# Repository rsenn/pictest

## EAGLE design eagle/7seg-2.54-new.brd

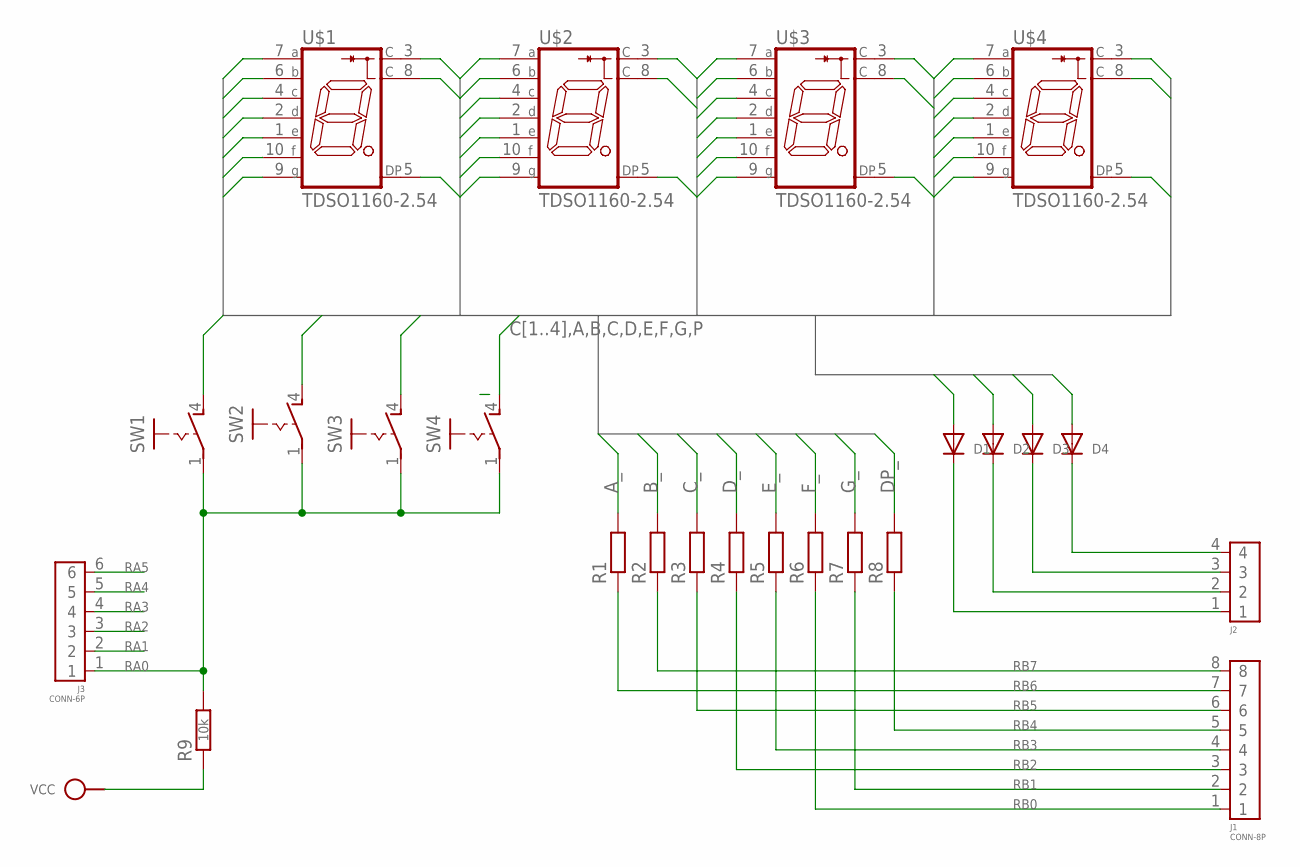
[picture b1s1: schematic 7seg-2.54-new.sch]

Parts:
D1, D2, D3, D4: 1N414834-2,5; DO34-2,5
J1: CONN-8P
J2: CONN-4P-4P; CONN-4P
J3: CONN-6P
R1, R2, R3, R4, R5, R6, R7, R8: R0202/5-V; 0202/5-V
R9: 10k; 0202/5-V
SW1, SW2, SW3, SW4: PB-1P-1T2P1T-2X3; PB-2P1T-2X3
U$1, U$2, U$3, U$4: TDSO1160-2.54; TDSX1150-2.54
VCC: SPAD

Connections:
A_: R1.2, U$1.7 (A), U$2.7 (A), U$3.7 (A), U$4.7 (A)
B_: R2.2, U$1.6 (B), U$2.6 (B), U$3.6 (B), U$4.6 (B)
C1: D1.A, SW1.4 (S), U$1.3 (C), U$1.8 (C)
C2: D2.A, SW2.4 (S), U$2.3 (C), U$2.8 (C)
C3: D3.A, SW3.4 (S), U$3.3 (C), U$3.8 (C)
C4: D4.A, SW4.4 (S), U$4.3 (C), U$4.8 (C)
C_: R3.2, U$1.4 (C), U$2.4 (C), U$3.4 (C), U$4.4 (C)
DP_: R8.2, U$1.5 (DP), U$2.5 (DP), U$3.5 (DP), U$4.5 (DP)
D_: R4.2, U$1.2 (D), U$2.2 (D), U$3.2 (D), U$4.2 (D)
E_: R5.2, U$1.1 (E), U$2.1 (E), U$3.1 (E), U$4.1 (E)
F_: R6.2, U$1.10 (F), U$2.10 (F), U$3.10 (F), U$4.10 (F)
G_: R7.2, U$1.9 (G), U$2.9 (G), U$3.9 (G), U$4.9 (G)
unnamed: D4.C, J2.4
unnamed: D3.C, J2.3
unnamed: D2.C, J2.2
unnamed: D1.C, J2.1
unnamed: R9.1, VCC.1
RA0: J3.1, R9.2, SW1.1, SW2.1, SW3.1, SW4.1
RA1: J3.2
RA2: J3.3
RA3: J3.4
RA4: J3.5
RA5: J3.6
RB0: J1.1, R6.1
RB1: J1.2, R7.1
RB2: J1.3, R4.1
RB3: J1.4, R5.1
RB4: J1.5, R8.1
RB5: J1.6, R3.1
RB6: J1.7, R1.1
RB7: J1.8, R2.1

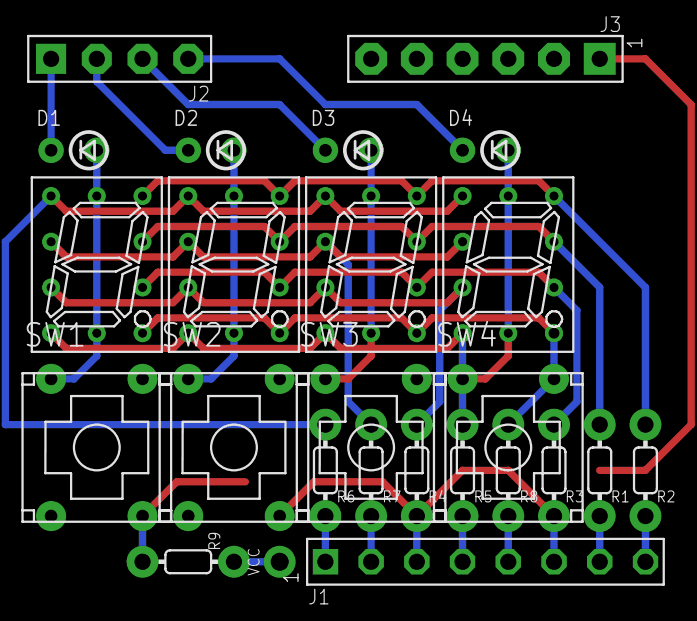
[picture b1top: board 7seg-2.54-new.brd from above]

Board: 2 copper layers, 25 parts (0 on the bottom side), 26 nets.

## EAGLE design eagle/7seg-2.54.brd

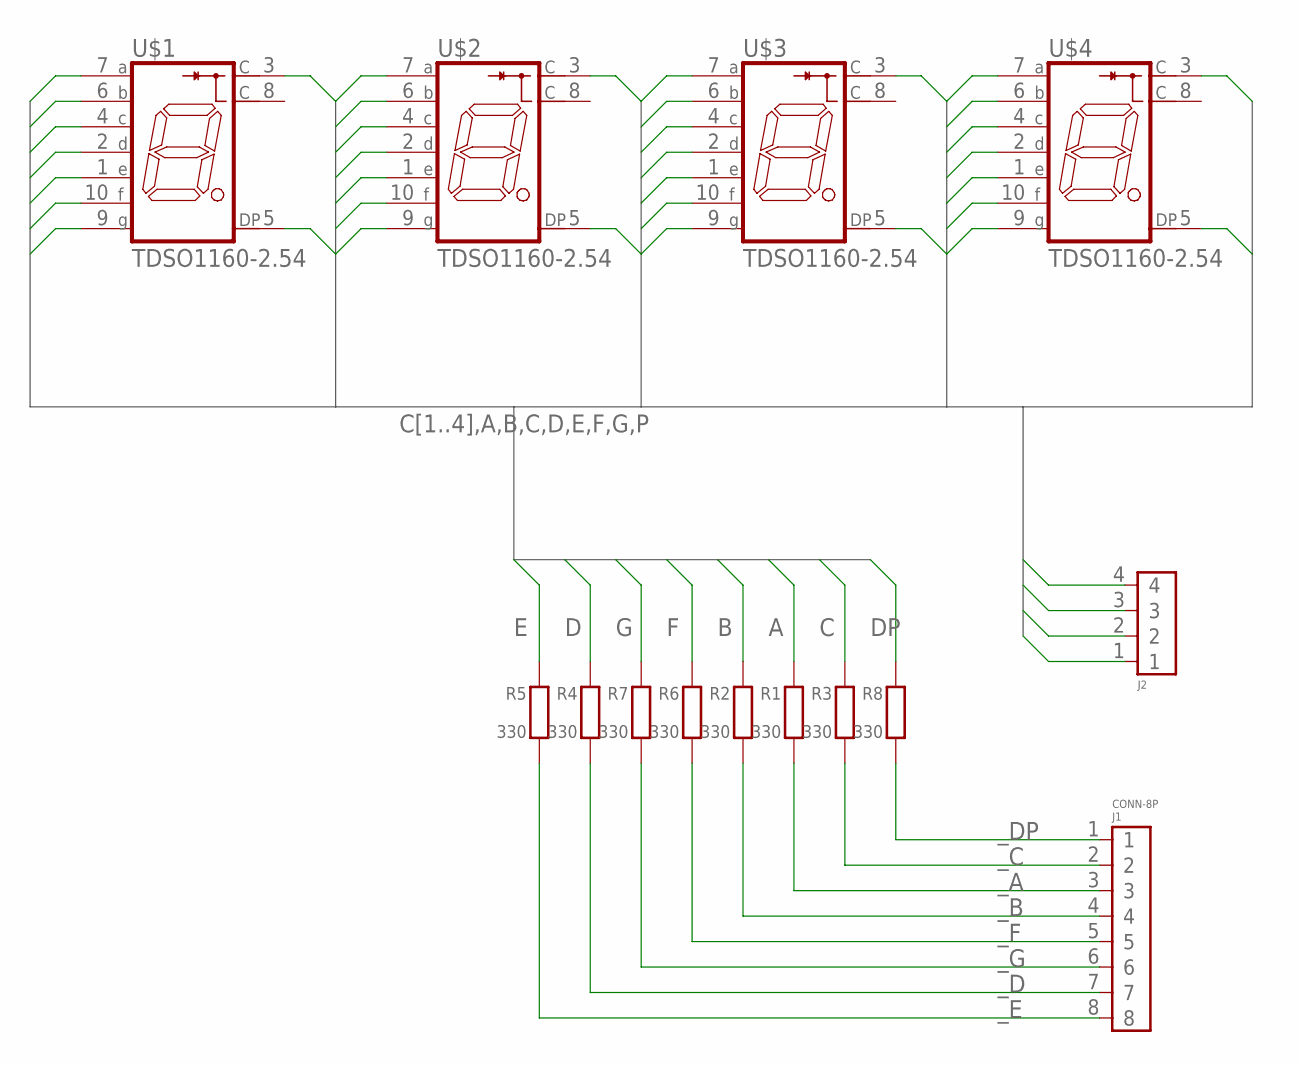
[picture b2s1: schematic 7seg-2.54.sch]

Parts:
J1: CONN-8P
J2: CONN-4P-4P; CONN-4P
R1, R2, R3, R4, R5, R6, R7, R8: 330; 0202/5-V
U$1, U$2, U$3, U$4: TDSO1160-2.54; TDSX1150-2.54

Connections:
A: R1.1 (2), U$1.7 (A), U$2.7 (A), U$3.7 (A), U$4.7 (A)
B: R2.1 (2), U$1.6 (B), U$2.6 (B), U$3.6 (B), U$4.6 (B)
C: R3.1 (2), U$1.4 (C), U$2.4 (C), U$3.4 (C), U$4.4 (C)
C1: J2.1, U$1.3 (C)
C2: J2.2, U$2.3 (C)
C3: J2.3, U$3.3 (C)
C4: J2.4, U$4.3 (C)
D: R4.1 (2), U$1.2 (D), U$2.2 (D), U$3.2 (D), U$4.2 (D)
DP: R8.1 (2), U$1.5 (DP), U$2.5 (DP), U$3.5 (DP), U$4.5 (DP)
E: R5.1 (2), U$1.1 (E), U$2.1 (E), U$3.1 (E), U$4.1 (E)
F: R6.1 (2), U$1.10 (F), U$2.10 (F), U$3.10 (F), U$4.10 (F)
G: R7.1 (2), U$1.9 (G), U$2.9 (G), U$3.9 (G), U$4.9 (G)
_A: J1.3, R1.2 (1)
_B: J1.4, R2.2 (1)
_C: J1.2, R3.2 (1)
_D: J1.7, R4.2 (1)
_DP: J1.1, R8.2 (1)
_E: J1.8, R5.2 (1)
_F: J1.5, R6.2 (1)
_G: J1.6, R7.2 (1)

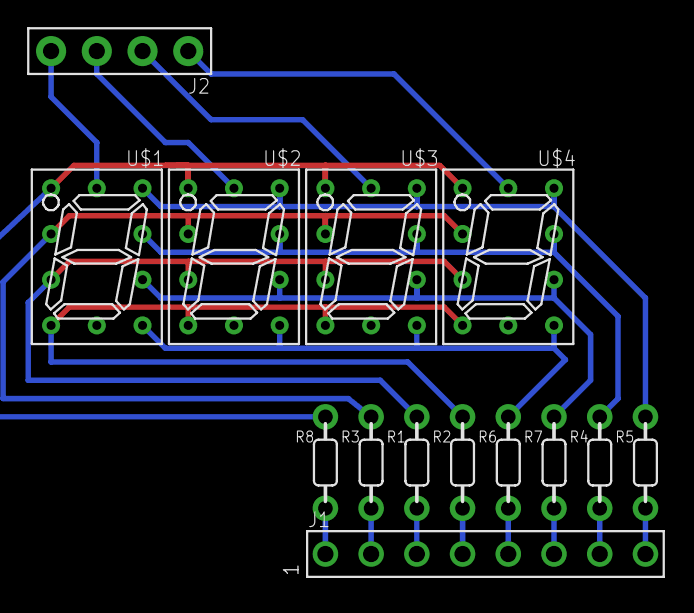
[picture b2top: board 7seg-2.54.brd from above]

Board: 2 copper layers, 14 parts (0 on the bottom side), 20 nets.

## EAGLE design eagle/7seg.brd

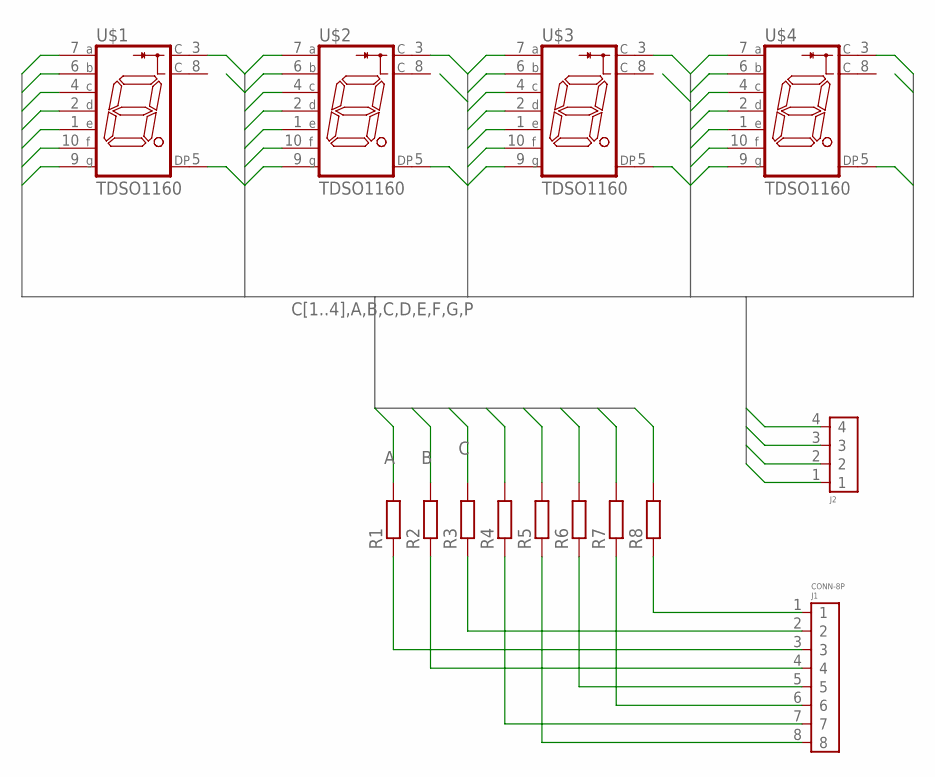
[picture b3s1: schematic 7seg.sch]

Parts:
J1: CONN-8P
J2: CONN-4P-4P; CONN-4P
R1, R2, R3, R4, R5, R6, R7, R8: R0202/7-V; 0202/7-V
U$1, U$2, U$3, U$4: TDSO1160; TDSX1150

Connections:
A: R1.2, U$1.7 (A), U$2.7 (A), U$3.7 (A), U$4.7 (A)
B: R2.2, U$1.6 (B), U$2.6 (B), U$3.6 (B), U$4.6 (B)
C: R3.2, U$1.4 (C), U$2.4 (C), U$3.4 (C), U$4.4 (C)
C1: J2.1, U$1.3 (C)
C2: J2.2, U$2.3 (C)
C3: J2.3, U$3.3 (C)
C4: J2.4, U$4.3 (C)
D: R4.2, U$1.2 (D), U$2.2 (D), U$3.2 (D), U$4.2 (D)
E: R5.2, U$1.1 (E), U$2.1 (E), U$3.1 (E), U$4.1 (E)
F: R6.2, U$1.10 (F), U$2.10 (F), U$3.10 (F), U$4.10 (F)
G: R7.2, U$1.9 (G), U$2.9 (G), U$3.9 (G), U$4.9 (G)
unnamed: J1.3, R1.1
unnamed: J1.4, R2.1
unnamed: J1.2, R3.1
unnamed: J1.7, R4.1
unnamed: J1.8, R5.1
unnamed: J1.5, R6.1
unnamed: J1.6, R7.1
unnamed: J1.1, R8.1
P: R8.2, U$1.5 (DP), U$2.5 (DP), U$3.5 (DP), U$4.5 (DP)

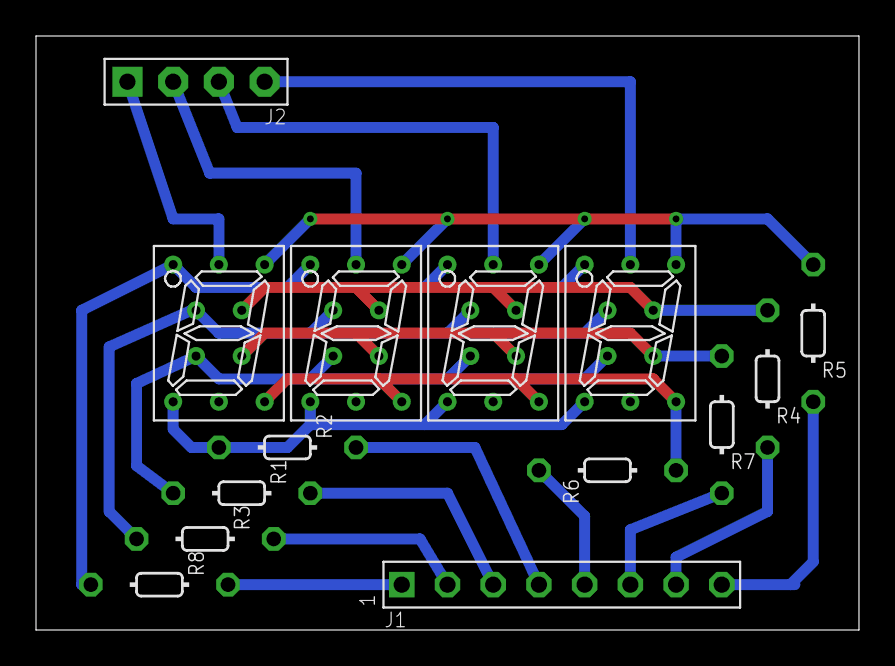
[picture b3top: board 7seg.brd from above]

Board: 2 copper layers, 45.7 x 33.0 mm, 14 parts (0 on the bottom side), 20 nets.

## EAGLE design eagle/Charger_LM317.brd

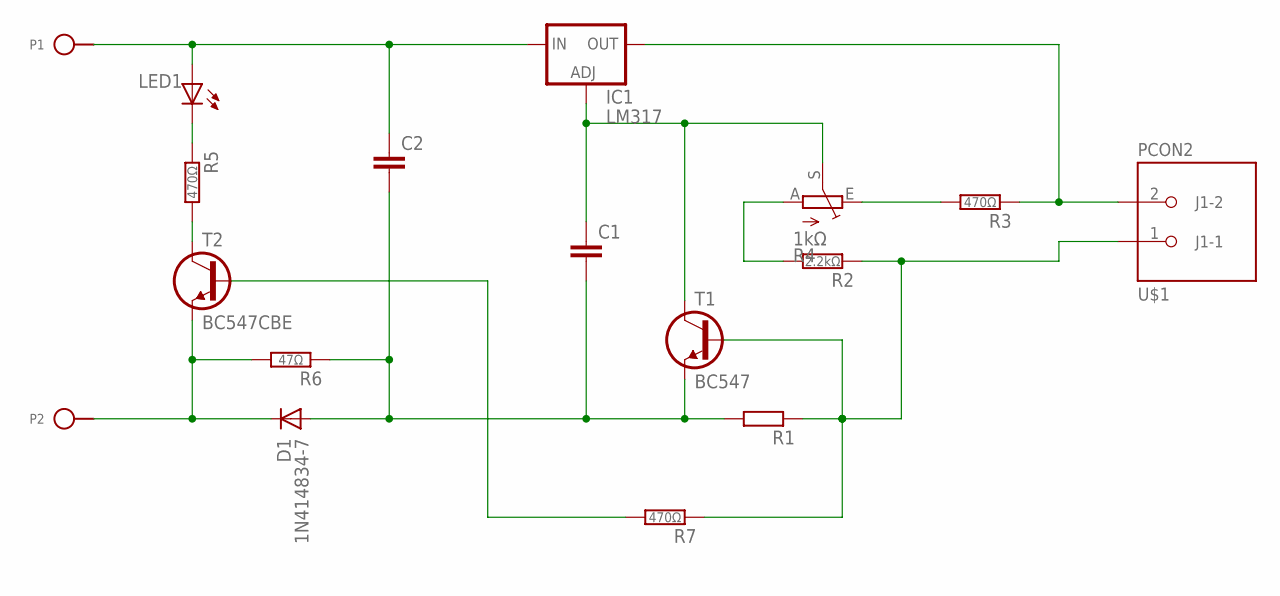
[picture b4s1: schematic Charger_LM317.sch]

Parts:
C1, C2: C050-020X036
D1: 1N414834-7; DO34-7
IC1: LM317; 317TL
LED1: LED5MM
P1: +; SPAD
P2: -; SPAD
R1: R0207/7; 0207/7
R2: 2.2kΩ; 0202/5
R3, R5, R7: 470Ω; 0202/7
R4: 1kΩ; B25P
R6: 47Ω; 0202/7
T1: BC547; TO92-CBE
T2: BC547CBE; TO92-CBE
U$1: PCON2; CON-2PIN

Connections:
ADJ: C1.1, IC1.1 (ADJ), R4.S, T1.C
GND: D1.C, P2.1, R6.2, T2.E
GND-: C1.2, C2.2, D1.A, R1.2, R6.1, T1.E
unnamed: R3.2, R4.E
unnamed: R2.2, R4.A
unnamed: R5.2, T2.C
unnamed: LED1.K (C), R5.1
unnamed: R7.2, T2.B
OUT+: IC1.2 (OUT), R3.1, U$1.2 (J1-2)
OUT-: R1.1, R2.1, R7.1, T1.B, U$1.1 (J1-1)
VCC: C2.1, IC1.3 (IN), LED1.A, P1.1

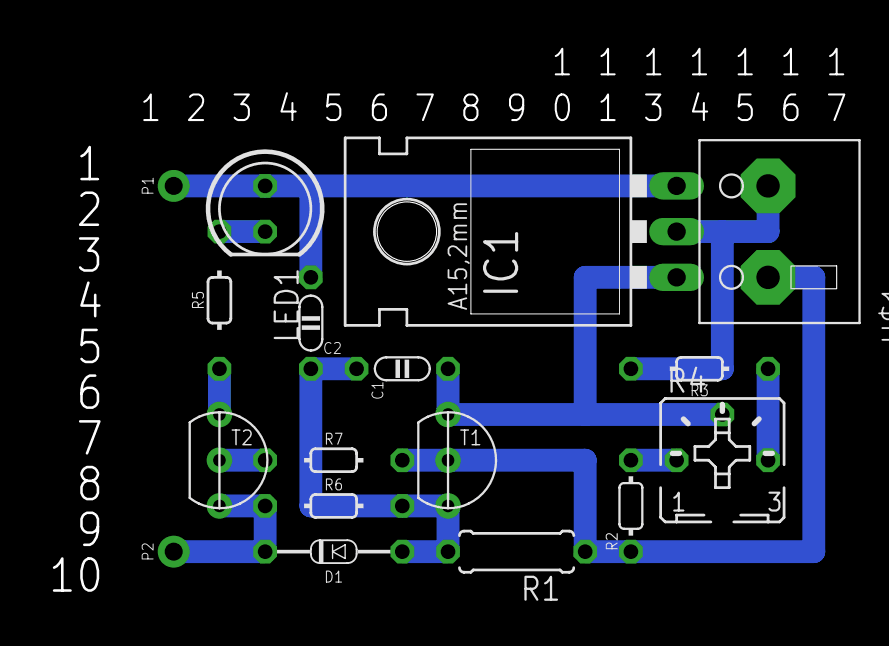
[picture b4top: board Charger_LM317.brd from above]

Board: 2 copper layers, 17 parts (0 on the bottom side), 11 nets.

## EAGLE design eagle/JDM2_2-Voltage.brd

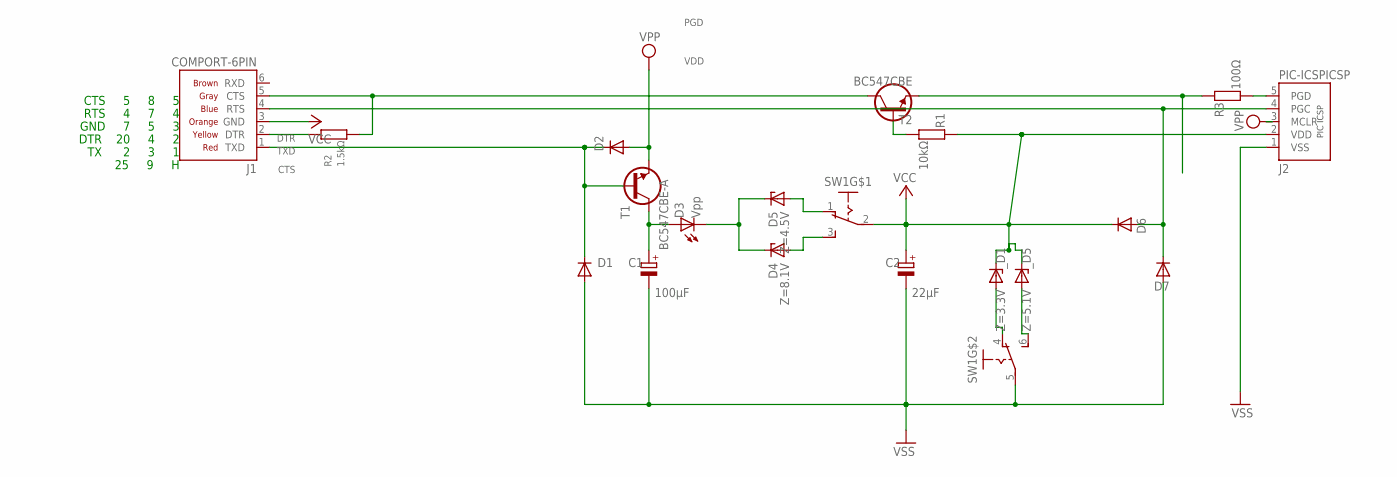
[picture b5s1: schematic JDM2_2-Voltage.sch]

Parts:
C1: 100μF; E5-4
C2: 22μF; E2,5-4
D1, D2: 1N4148; DO34-5
D3: Vpp; LED3MM
D4: Z=8.1V; DO34Z5
D5: Z=4.5V; DO34Z5
D6, D7: 1N4148; DO34-7
J1: COMPORT-6PIN; RS232-6PIN
J2: PIC-ICSPICSP; PIC-ICSP
R1: 10kΩ; 0202/7
R2: 1.5kΩ; 0202/7
R3: 100Ω; 0202/5
SW1: SL-SW-2P-2T-S; SLSW-2P2T-H
T1: BC547CBE-A; TO92-CBE-A
T2: BC547CBE; TO92-CBE
_D1: Z=3.3V; DO34Z5
_D5: Z=5.1V; DO34Z5

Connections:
/MCLR: D2.A, J2.3 (MCLR), T1.E
CLK: D6.A, D7.C, J1.4 (RTS), J2.4 (PGC)
CTS: J1.5 (CTS), R2.2, T2.C
DATA: R3.2, T2.E
DTR: J1.2 (DTR), R2.1
unnamed: R1.1, T2.B
unnamed: SW1.4 (O), _D1.A
unnamed: SW1.6 (S), _D5.A
unnamed: D5.A, SW1.1 (O)
unnamed: D3.K (C), D4.C, D5.C
unnamed: D4.A, SW1.3 (S)
PGD: J2.5 (PGD), R3.1
TXD: D1.C, D2.C, J1.1 (TXD), T1.B
VDD: C2.+, D6.C, J1.3 (GND), J2.2 (VDD), R1.2, SW1.2, _D1.C, _D5.C
VPP: C1.+, D3.A, T1.C
VSS: C1.-, C2.-, D1.A, D7.A, J2.1 (VSS), SW1.5

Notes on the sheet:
DTR 20 4 2
TX 2 3 1
CTS 5 8 5
GND 7 5 3
RTS 4 7 4
25 9 H

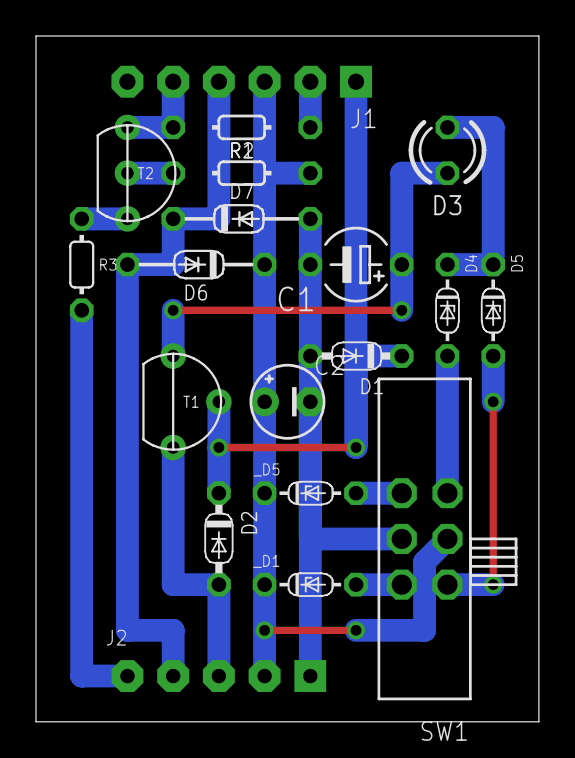
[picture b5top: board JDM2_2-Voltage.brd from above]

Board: 2 copper layers, 27.9 x 38.1 mm, 19 parts (0 on the bottom side), 16 nets.

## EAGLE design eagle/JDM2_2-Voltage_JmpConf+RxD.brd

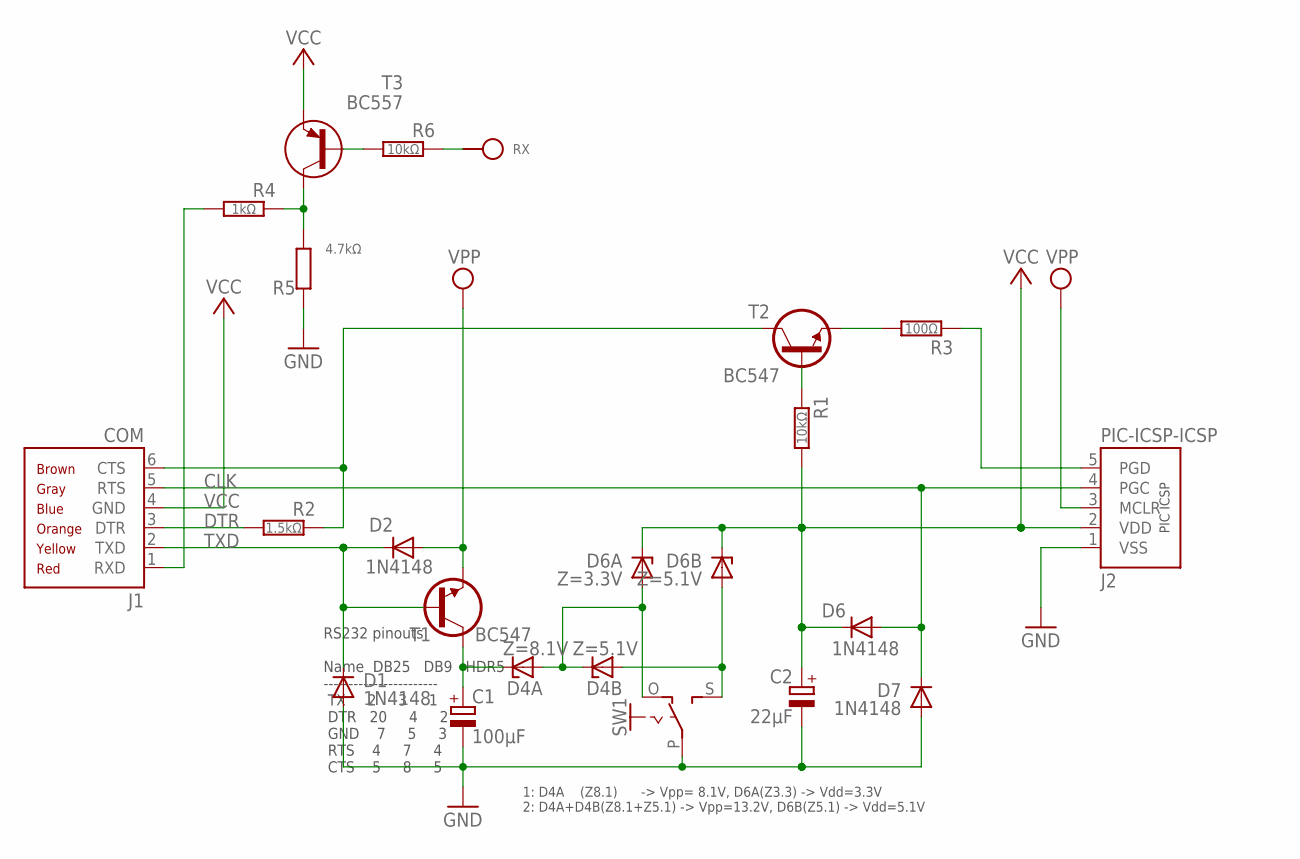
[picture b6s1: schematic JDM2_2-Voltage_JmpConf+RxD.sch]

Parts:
C1: 100μF; E2,5-5/V
C2: 22μF; E2.5-4/V
D1, D6: 1N4148; DO34-5V
D2: 1N4148; DO34-5
D4A: Z=8.1V; DO34Z5
D4B: Z=5.1V; DO34Z5
D6A: Z=3.3V; DO34Z7V
D6B: Z=5.1V; DO34Z7V
D7: 1N4148; DO34-7V
J1: COM; RS232-6PIN-NEW-L
J2: PIC-ICSP-ICSP; PIC-ICSP
R1: 10kΩ; 0202/7-V
R2: 1.5kΩ; 0202/7-V
R3: 100Ω; 0202/7
R4: 1kΩ; 0202/5-V
R5: 4.7kΩ; 0202/5
R6: 10kΩ; 0202/5
RX: RX; SPAD
SW1: SL-SW-1P-2T-JPSW; JPSW-1P2T
T1, T2: BC547; TO92-CBE@1
T3: BC557; TO92-CBE

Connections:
/MCLR: D2.A, J2.3 (MCLR), T1.E
CLK: D6.A, D7.C, J1.5 (RTS), J2.4 (PGC)
CTS: J1.6 (CTS), R2.1, T2.C
DATA: R3.2, T2.E
DTR: J1.3 (DTR), R2.2
GND: C1.-, C2.-, D1.A, D7.A, J2.1 (VSS), R5.1, SW1.P
unnamed: R1.1, T2.B
unnamed: J1.1 (RXD), R4.2
unnamed: D4B.A, D6B.A, SW1.S
unnamed: D4A.A, D4B.C, D6A.A, SW1.O
unnamed: R6.2, T3.B
unnamed: R4.1, R5.2, T3.C
PGD: J2.5 (PGD), R3.1
RXD: R6.1, RX.1
TXD: D1.C, D2.C, J1.2 (TXD), T1.B
VCC: C2.+, D6.C, D6A.C, D6B.C, J1.4 (GND), J2.2 (VDD), R1.2, T3.E
VPP: C1.+, D4A.C, T1.C

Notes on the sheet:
RS232 pinouts Name DB25 DB9 HDR5 ----------------------- TX 2 3 1 DTR 20 4 2 GND 7 5 3 RTS 4 7 4 CTS 5 8 5
1: D4A (Z8.1) -> Vpp= 8.1V, D6A(Z3.3) -> Vdd=3.3V 2: D4A+D4B(Z8.1+Z5.1) -> Vpp=13.2V, D6B(Z5.1) -> Vdd=5.1V

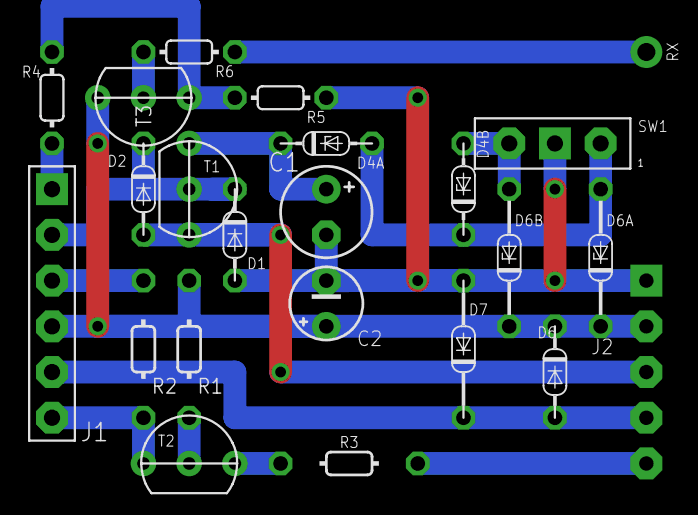
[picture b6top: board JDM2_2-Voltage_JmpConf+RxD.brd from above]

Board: 2 copper layers, 23 parts (0 on the bottom side), 17 nets.
